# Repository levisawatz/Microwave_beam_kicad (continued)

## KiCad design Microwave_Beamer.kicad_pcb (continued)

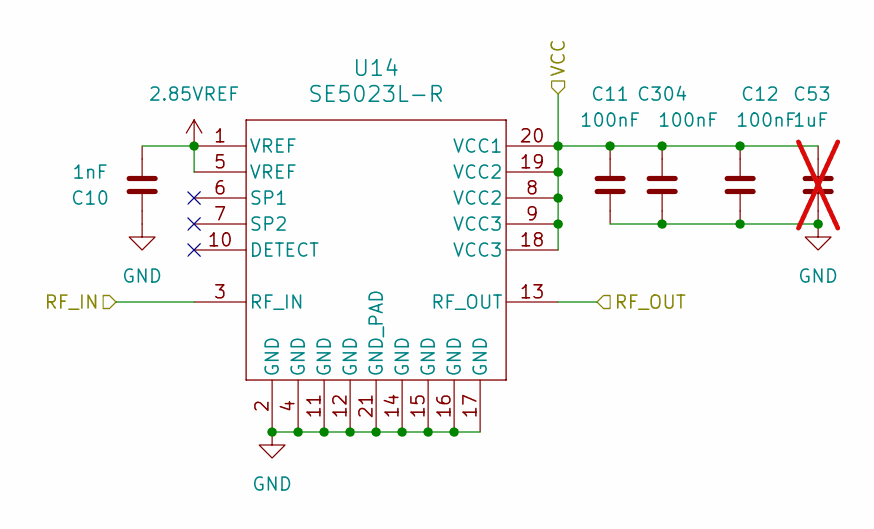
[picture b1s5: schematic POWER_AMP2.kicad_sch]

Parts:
C10: 1nF; C_0402_1005Metric; MPN GCM1555C1H102GA16J
C11, C12, C304: 100nF; C_0402_1005Metric; MPN GCM155R71H104KE02J
C53: 1uF; C_0603_1608Metric; MPN GRT188R61H105KE13D; not fitted
U14: SE5023L-R; QFN20_4X4_STM; MPN SE5023L-R

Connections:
2.85VREF: C10.1, U14.1 (VREF), U14.5 (VREF); also elsewhere on the board
+5V: C11.1, C12.1, C53.1, C304.1, U14.8 (VCC2), U14.9 (VCC3), U14.18 (VCC3), U14.19 (VCC2), U14.20 (VCC1); also elsewhere on the board
/STEM/FAN_A/Antenna_2: U14.13 (RF_OUT)
/STEM/FAN_A/FANFAN A/OUT2: U14.3 (RF_IN); also elsewhere on the board
GND: C10.2, C11.2, C12.2, C53.2, C304.2, U14.2 (GND), U14.4 (GND), U14.11 (GND), U14.12 (GND), U14.14 (GND), U14.15 (GND), U14.16 (GND), U14.17 (GND), U14.21 (GND_PAD); also elsewhere on the board

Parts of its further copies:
C13, C14, C15, C16, C18, C19, C20, C21, C22, C23, C32, C33, C34, C35, C36, C37, C70, C71, C81, C82, C84, C85, C95, C96, C98, C99, C106, C107, C110, C111, C113, C114, C118, C119, C305, C306, C307, C308, C309, C310, C311, C312, C313, C314, C315, C316, C317, C318, C319, C320, C321: 100nF; C_0402_1005Metric; MPN GCM155R71H104KE02J
C17, C31, C52, C66, C80, C94, C108, C122, C136, C150, C164, C178, C192, C206, C220, C234, C248: 1nF; C_0402_1005Metric; MPN GCM1555C1H102GA16J
C54, C55, C56, C57, C58, C67, C68, C69, C72, C83, C86, C97, C100, C109, C112, C116, C120: 1uF; C_0603_1608Metric; MPN GRT188R61H105KE13D; not fitted
U15, U17, U20, U22, U24, U26, U28, U30, U32, U34, U36, U38, U40, U42, U44, U46, U48: SE5023L-R; QFN20_4X4_STM; MPN SE5023L-R

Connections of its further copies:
2.85VREF: C17.1, C31.1, C52.1, C66.1, C80.1, C94.1, C108.1, C122.1, C136.1, C150.1, C164.1, C178.1, C192.1, C206.1, C220.1, C234.1, C248.1, U15.1 (VREF), U15.5 (VREF), U17.1 (VREF), U17.5 (VREF), U20.1 (VREF), U20.5 (VREF), U22.1 (VREF), U22.5 (VREF), U24.1 (VREF), U24.5 (VREF), U26.1 (VREF), U26.5 (VREF), U28.1 (VREF), U28.5 (VREF), U30.1 (VREF), U30.5 (VREF), U32.1 (VREF), U32.5 (VREF), U34.1 (VREF), U34.5 (VREF), U36.1 (VREF), U36.5 (VREF), U38.1 (VREF), U38.5 (VREF), U40.1 (VREF), U40.5 (VREF), U42.1 (VREF), U42.5 (VREF), U44.1 (VREF), U44.5 (VREF), U46.1 (VREF), U46.5 (VREF), U48.1 (VREF), U48.5 (VREF); also elsewhere on the board
+5V: C13.1, C14.1, C15.1, C16.1, C18.1, C19.1, C20.1, C21.1, C22.1, C23.1, C32.1, C33.1, C34.1, C35.1, C36.1, C37.1, C54.1, C55.1, C56.1, C57.1, C58.1, C67.1, C68.1, C69.1, C70.1, C71.1, C72.1, C81.1, C82.1, C83.1, C84.1, C85.1, C86.1, C95.1, C96.1, C97.1, C98.1, C99.1, C100.1, C106.1, C107.1, C109.1, C110.1, C111.1, C112.1, C113.1, C114.1, C116.1, C118.1, C119.1, C120.1, C305.1, C306.1, C307.1, C308.1, C309.1, C310.1, C311.1, C312.1, C313.1, C314.1, C315.1, C316.1, C317.1, C318.1, C319.1, C320.1, C321.1, U15.8 (VCC2), U15.9 (VCC3), U15.18 (VCC3), U15.19 (VCC2), U15.20 (VCC1), U17.8 (VCC2), U17.9 (VCC3), U17.18 (VCC3), U17.19 (VCC2), U17.20 (VCC1), U20.8 (VCC2), U20.9 (VCC3), U20.18 (VCC3), U20.19 (VCC2), U20.20 (VCC1), U22.8 (VCC2), U22.9 (VCC3), U22.18 (VCC3), U22.19 (VCC2), U22.20 (VCC1), U24.8 (VCC2), U24.9 (VCC3), U24.18 (VCC3), U24.19 (VCC2), U24.20 (VCC1), U26.8 (VCC2), U26.9 (VCC3), U26.18 (VCC3), U26.19 (VCC2), U26.20 (VCC1), U28.8 (VCC2), U28.9 (VCC3), U28.18 (VCC3), U28.19 (VCC2), U28.20 (VCC1), U30.8 (VCC2), U30.9 (VCC3), U30.18 (VCC3), U30.19 (VCC2), U30.20 (VCC1), U32.8 (VCC2), U32.9 (VCC3), U32.18 (VCC3), U32.19 (VCC2), U32.20 (VCC1), U34.8 (VCC2), U34.9 (VCC3), U34.18 (VCC3), U34.19 (VCC2), U34.20 (VCC1), U36.8 (VCC2), U36.9 (VCC3), U36.18 (VCC3), U36.19 (VCC2), U36.20 (VCC1), U38.8 (VCC2), U38.9 (VCC3), U38.18 (VCC3), U38.19 (VCC2), U38.20 (VCC1), U40.8 (VCC2), U40.9 (VCC3), U40.18 (VCC3), U40.19 (VCC2), U40.20 (VCC1), U42.8 (VCC2), U42.9 (VCC3), U42.18 (VCC3), U42.19 (VCC2), U42.20 (VCC1), U44.8 (VCC2), U44.9 (VCC3), U44.18 (VCC3), U44.19 (VCC2), U44.20 (VCC1), U46.8 (VCC2), U46.9 (VCC3), U46.18 (VCC3), U46.19 (VCC2), U46.20 (VCC1), U48.8 (VCC2), U48.9 (VCC3), U48.18 (VCC3), U48.19 (VCC2), U48.20 (VCC1); also elsewhere on the board
/STEM/FAN_A/Antenna_4: U15.13 (RF_OUT)
/STEM/FAN_A/Antenna_6: U17.13 (RF_OUT)
/STEM/FAN_A/FANFAN A/OUT4: U15.3 (RF_IN); also elsewhere on the board
/STEM/FAN_A/FANFAN A/OUT6: U17.3 (RF_IN); also elsewhere on the board
/STEM/FAN_B/Antenna_2: U20.13 (RF_OUT)
/STEM/FAN_B/Antenna_4: U24.13 (RF_OUT)
/STEM/FAN_B/Antenna_6: U22.13 (RF_OUT)
/STEM/FAN_B/FANFAN A/OUT2: U20.3 (RF_IN); also elsewhere on the board
/STEM/FAN_B/FANFAN A/OUT4: U24.3 (RF_IN); also elsewhere on the board
/STEM/FAN_B/FANFAN A/OUT6: U22.3 (RF_IN); also elsewhere on the board
/STEM/FAN_C/Antenna_2: U26.13 (RF_OUT)
/STEM/FAN_C/Antenna_4: U30.13 (RF_OUT)
/STEM/FAN_C/Antenna_6: U28.13 (RF_OUT)
/STEM/FAN_C/FANFAN A/OUT2: U26.3 (RF_IN); also elsewhere on the board
/STEM/FAN_C/FANFAN A/OUT4: U30.3 (RF_IN); also elsewhere on the board
/STEM/FAN_C/FANFAN A/OUT6: U28.3 (RF_IN); also elsewhere on the board
/STEM/FAN_D/Antenna_2: U32.13 (RF_OUT)
/STEM/FAN_D/Antenna_4: U36.13 (RF_OUT)
/STEM/FAN_D/Antenna_6: U34.13 (RF_OUT)
/STEM/FAN_D/FANFAN A/OUT2: U32.3 (RF_IN); also elsewhere on the board
/STEM/FAN_D/FANFAN A/OUT4: U36.3 (RF_IN); also elsewhere on the board
/STEM/FAN_D/FANFAN A/OUT6: U34.3 (RF_IN); also elsewhere on the board
/STEM/FAN_E/Antenna_2: U38.13 (RF_OUT)
/STEM/FAN_E/Antenna_4: U42.13 (RF_OUT)
/STEM/FAN_E/Antenna_6: U40.13 (RF_OUT)
/STEM/FAN_E/FANFAN A/OUT2: U38.3 (RF_IN); also elsewhere on the board
/STEM/FAN_E/FANFAN A/OUT4: U42.3 (RF_IN); also elsewhere on the board
/STEM/FAN_E/FANFAN A/OUT6: U40.3 (RF_IN); also elsewhere on the board
/STEM/FAN_F/Antenna_2: U44.13 (RF_OUT)
/STEM/FAN_F/Antenna_4: U48.13 (RF_OUT)
/STEM/FAN_F/Antenna_6: U46.13 (RF_OUT)
/STEM/FAN_F/FANFAN A/OUT2: U44.3 (RF_IN); also elsewhere on the board
/STEM/FAN_F/FANFAN A/OUT4: U48.3 (RF_IN); also elsewhere on the board
/STEM/FAN_F/FANFAN A/OUT6: U46.3 (RF_IN); also elsewhere on the board
GND: C13.2, C14.2, C15.2, C16.2, C17.2, C18.2, C19.2, C20.2, C21.2, C22.2, C23.2, C31.2, C32.2, C33.2, C34.2, C35.2, C36.2, C37.2, C52.2, C54.2, C55.2, C56.2, C57.2, C58.2, C66.2, C67.2, C68.2, C69.2, C70.2, C71.2, C72.2, C80.2, C81.2, C82.2, C83.2, C84.2, C85.2, C86.2, C94.2, C95.2, C96.2, C97.2, C98.2, C99.2, C100.2, C106.2, C107.2, C108.2, C109.2, C110.2, C111.2, C112.2, C113.2, C114.2, C116.2, C118.2, C119.2, C120.2, C122.2, C136.2, C150.2, C164.2, C178.2, C192.2, C206.2, C220.2, C234.2, C248.2, C305.2, C306.2, C307.2, C308.2, C309.2, C310.2, C311.2, C312.2, C313.2, C314.2, C315.2, C316.2, C317.2, C318.2, C319.2, C320.2, C321.2, U15.2 (GND), U15.4 (GND), U15.11 (GND), U15.12 (GND), U15.14 (GND), U15.15 (GND), U15.16 (GND), U15.17 (GND), U15.21 (GND_PAD), U17.2 (GND), U17.4 (GND), U17.11 (GND), U17.12 (GND), U17.14 (GND), U17.15 (GND), U17.16 (GND), U17.17 (GND), U17.21 (GND_PAD), U20.2 (GND), U20.4 (GND), U20.11 (GND), U20.12 (GND), U20.14 (GND), U20.15 (GND), U20.16 (GND), U20.17 (GND), U20.21 (GND_PAD), U22.2 (GND), U22.4 (GND), U22.11 (GND), U22.12 (GND), U22.14 (GND), U22.15 (GND), U22.16 (GND), U22.17 (GND), U22.21 (GND_PAD), U24.2 (GND), U24.4 (GND), U24.11 (GND), U24.12 (GND), U24.14 (GND), U24.15 (GND), U24.16 (GND), U24.17 (GND), U24.21 (GND_PAD), U26.2 (GND), U26.4 (GND), U26.11 (GND), U26.12 (GND), U26.14 (GND), U26.15 (GND), U26.16 (GND), U26.17 (GND), U26.21 (GND_PAD), U28.2 (GND), U28.4 (GND), U28.11 (GND), U28.12 (GND), U28.14 (GND), U28.15 (GND), U28.16 (GND), U28.17 (GND), U28.21 (GND_PAD), U30.2 (GND), U30.4 (GND), U30.11 (GND), U30.12 (GND), U30.14 (GND), U30.15 (GND), U30.16 (GND), U30.17 (GND), U30.21 (GND_PAD), U32.2 (GND), U32.4 (GND), U32.11 (GND), U32.12 (GND), U32.14 (GND), U32.15 (GND), U32.16 (GND), U32.17 (GND), U32.21 (GND_PAD), U34.2 (GND), U34.4 (GND), U34.11 (GND), U34.12 (GND), U34.14 (GND), U34.15 (GND), U34.16 (GND), U34.17 (GND), U34.21 (GND_PAD), U36.2 (GND), U36.4 (GND), U36.11 (GND), U36.12 (GND), U36.14 (GND), U36.15 (GND), U36.16 (GND), U36.17 (GND), U36.21 (GND_PAD), U38.2 (GND), U38.4 (GND), U38.11 (GND), U38.12 (GND), U38.14 (GND), U38.15 (GND), U38.16 (GND), U38.17 (GND), U38.21 (GND_PAD), U40.2 (GND), U40.4 (GND), U40.11 (GND), U40.12 (GND), U40.14 (GND), U40.15 (GND), U40.16 (GND), U40.17 (GND), U40.21 (GND_PAD), U42.2 (GND), U42.4 (GND), U42.11 (GND), U42.12 (GND), U42.14 (GND), U42.15 (GND), U42.16 (GND), U42.17 (GND), U42.21 (GND_PAD), U44.2 (GND), U44.4 (GND), U44.11 (GND), U44.12 (GND), U44.14 (GND), U44.15 (GND), U44.16 (GND), U44.17 (GND), U44.21 (GND_PAD), U46.2 (GND), U46.4 (GND), U46.11 (GND), U46.12 (GND), U46.14 (GND), U46.15 (GND), U46.16 (GND), U46.17 (GND), U46.21 (GND_PAD), U48.2 (GND), U48.4 (GND), U48.11 (GND), U48.12 (GND), U48.14 (GND), U48.15 (GND), U48.16 (GND), U48.17 (GND), U48.21 (GND_PAD); also elsewhere on the board

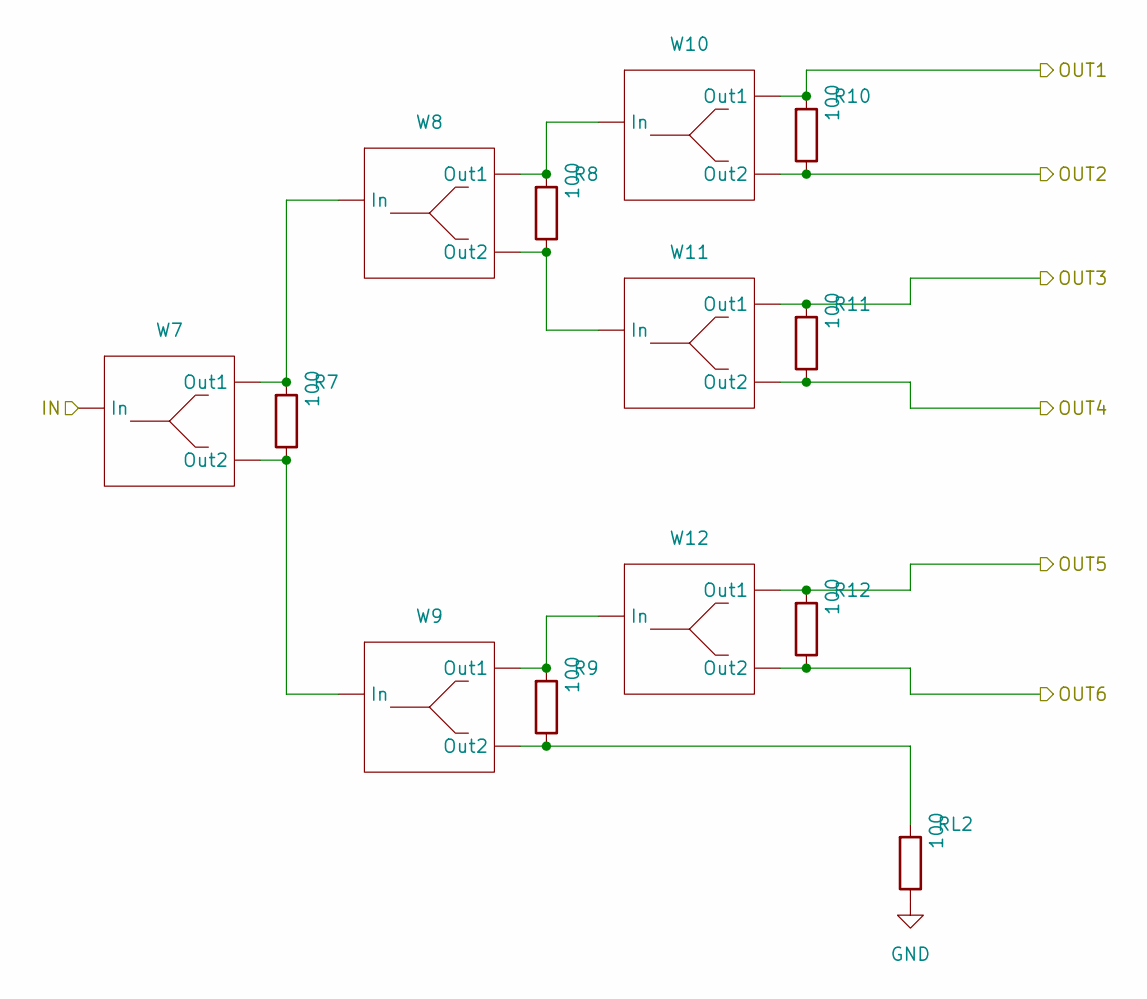
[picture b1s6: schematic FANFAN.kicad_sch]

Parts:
R7, R8, R9, R10, R11, R12: 100; R_0402_1005Metric; MPN ERA-2AED101X
RL2: 100; R_0402_1005Metric; MPN ERA-2AED101X
W7, W8, W9, W10, W11, W12: 50-70.7 Y

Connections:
/STEM/FAN_A/FANFAN A/OUT1: R10.1, W10.2 (Out1); also elsewhere on the board
/STEM/FAN_A/FANFAN A/OUT2: R10.2, W10.3 (Out2); also elsewhere on the board
/STEM/FAN_A/FANFAN A/OUT3: R11.1, W11.2 (Out1); also elsewhere on the board
/STEM/FAN_A/FANFAN A/OUT4: R11.2, W11.3 (Out2); also elsewhere on the board
/STEM/FAN_A/FANFAN A/OUT5: R12.1, W12.2 (Out1); also elsewhere on the board
/STEM/FAN_A/FANFAN A/OUT6: R12.2, W12.3 (Out2); also elsewhere on the board
/STEM/FAN_A/IN: W7.1 (In); also elsewhere on the board
GND: RL2.2; also elsewhere on the board
unnamed: R7.1, W7.2 (Out1), W8.1 (In)
unnamed: R7.2, W7.3 (Out2), W9.1 (In)
unnamed: R9.2, RL2.1, W9.3 (Out2)
unnamed: R8.1, W8.2 (Out1), W10.1 (In)
unnamed: R8.2, W8.3 (Out2), W11.1 (In)
unnamed: R9.1, W9.2 (Out1), W12.1 (In)

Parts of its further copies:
R13, R14, R15, R16, R17, R18, R19, R20, R21, R22, R23, R24, R25, R26, R27, R28, R29, R30, R31, R32, R33, R34, R35, R36, R37, R38, R39, R40, R41, R42: 100; R_0402_1005Metric; MPN ERA-2AED101X

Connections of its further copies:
/STEM/FAN_B/FANFAN A/OUT1: R16.1; also elsewhere on the board
/STEM/FAN_B/FANFAN A/OUT2: R16.2; also elsewhere on the board
/STEM/FAN_B/FANFAN A/OUT3: R17.1; also elsewhere on the board
/STEM/FAN_B/FANFAN A/OUT4: R17.2; also elsewhere on the board
/STEM/FAN_B/FANFAN A/OUT5: R18.1; also elsewhere on the board
/STEM/FAN_B/FANFAN A/OUT6: R18.2; also elsewhere on the board
/STEM/FAN_C/FANFAN A/OUT1: R22.1; also elsewhere on the board
/STEM/FAN_C/FANFAN A/OUT2: R22.2; also elsewhere on the board
/STEM/FAN_C/FANFAN A/OUT3: R23.1; also elsewhere on the board
/STEM/FAN_C/FANFAN A/OUT4: R23.2; also elsewhere on the board
/STEM/FAN_C/FANFAN A/OUT5: R24.1; also elsewhere on the board
/STEM/FAN_C/FANFAN A/OUT6: R24.2; also elsewhere on the board
/STEM/FAN_D/FANFAN A/OUT1: R28.1; also elsewhere on the board
/STEM/FAN_D/FANFAN A/OUT2: R28.2; also elsewhere on the board
/STEM/FAN_D/FANFAN A/OUT3: R29.1; also elsewhere on the board
/STEM/FAN_D/FANFAN A/OUT4: R29.2; also elsewhere on the board
/STEM/FAN_D/FANFAN A/OUT5: R30.1; also elsewhere on the board
/STEM/FAN_D/FANFAN A/OUT6: R30.2; also elsewhere on the board
/STEM/FAN_E/FANFAN A/OUT1: R34.1; also elsewhere on the board
/STEM/FAN_E/FANFAN A/OUT2: R34.2; also elsewhere on the board
/STEM/FAN_E/FANFAN A/OUT3: R35.1; also elsewhere on the board
/STEM/FAN_E/FANFAN A/OUT4: R35.2; also elsewhere on the board
/STEM/FAN_E/FANFAN A/OUT5: R36.1; also elsewhere on the board
/STEM/FAN_E/FANFAN A/OUT6: R36.2; also elsewhere on the board
/STEM/FAN_F/FANFAN A/OUT1: R40.1; also elsewhere on the board
/STEM/FAN_F/FANFAN A/OUT2: R40.2; also elsewhere on the board
/STEM/FAN_F/FANFAN A/OUT3: R41.1; also elsewhere on the board
/STEM/FAN_F/FANFAN A/OUT4: R41.2; also elsewhere on the board
/STEM/FAN_F/FANFAN A/OUT5: R42.1; also elsewhere on the board
/STEM/FAN_F/FANFAN A/OUT6: R42.2; also elsewhere on the board
unnamed 213: R13.1; also elsewhere on the board
unnamed 214: R13.2; also elsewhere on the board
unnamed 215: R14.1; also elsewhere on the board
unnamed 216: R14.2; also elsewhere on the board
unnamed 217: R15.1; also elsewhere on the board
unnamed 218: R15.2; also elsewhere on the board
unnamed 219: R19.1; also elsewhere on the board
unnamed 220: R19.2; also elsewhere on the board
unnamed 221: R20.1; also elsewhere on the board
unnamed 222: R20.2; also elsewhere on the board
unnamed 223: R21.1; also elsewhere on the board
unnamed 224: R21.2; also elsewhere on the board
unnamed 225: R25.1; also elsewhere on the board
unnamed 226: R25.2; also elsewhere on the board
unnamed 227: R26.1; also elsewhere on the board
unnamed 228: R26.2; also elsewhere on the board
unnamed 229: R27.1; also elsewhere on the board
unnamed 230: R27.2; also elsewhere on the board
unnamed 231: R31.1; also elsewhere on the board
unnamed 232: R31.2; also elsewhere on the board
unnamed 233: R32.1; also elsewhere on the board
unnamed 234: R32.2; also elsewhere on the board
unnamed 235: R33.1; also elsewhere on the board
unnamed 236: R33.2; also elsewhere on the board
unnamed 237: R37.1; also elsewhere on the board
unnamed 238: R37.2; also elsewhere on the board
unnamed 239: R38.1; also elsewhere on the board
unnamed 240: R38.2; also elsewhere on the board
unnamed 241: R39.1; also elsewhere on the board
unnamed 242: R39.2; also elsewhere on the board

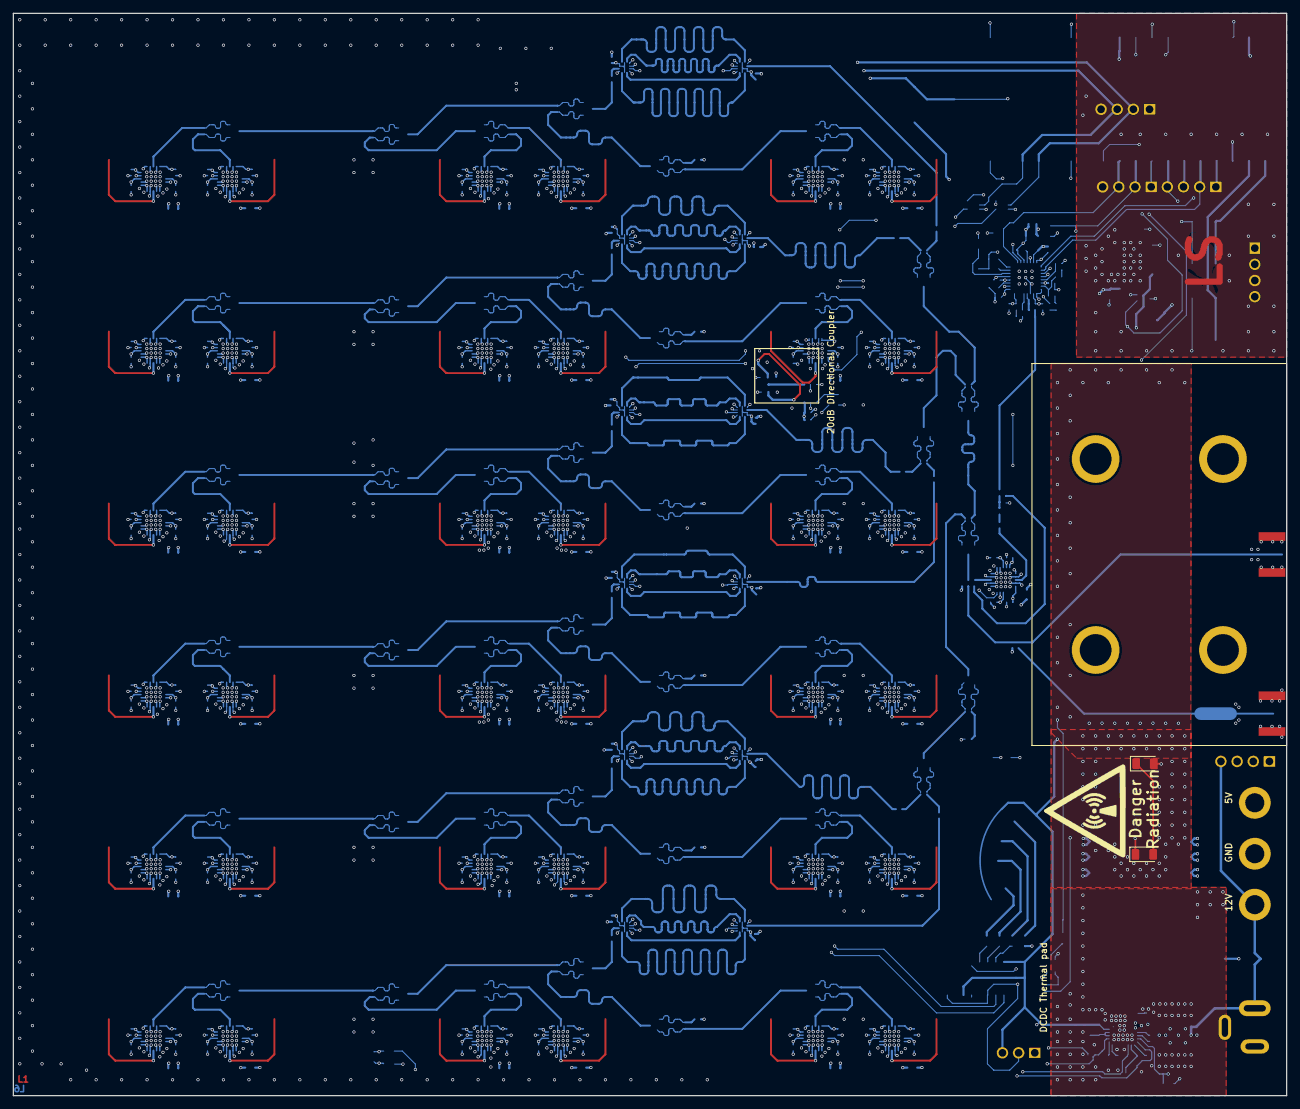
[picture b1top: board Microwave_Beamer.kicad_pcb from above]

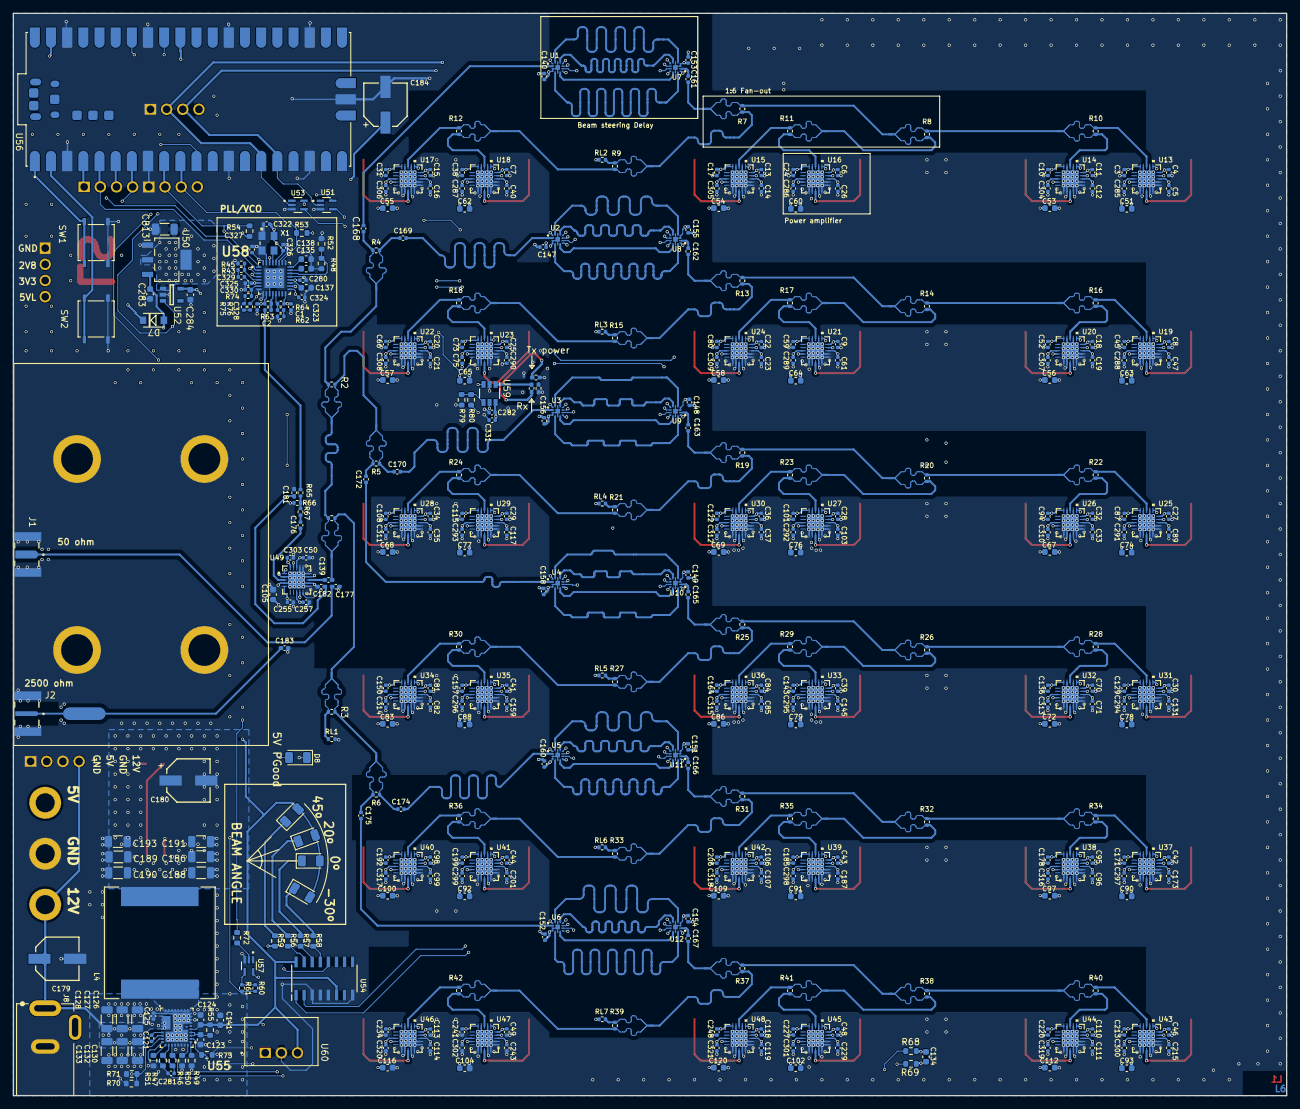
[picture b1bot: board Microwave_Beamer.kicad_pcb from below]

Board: 6 copper layers, 200.0 x 170.0 mm, 473 parts (464 on the bottom side), 198 nets.

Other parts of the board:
RL3, RL4, RL5, RL6, RL7: 50; R_0402_1005Metric
W13, W14, W15, W16, W17, W18, W19, W20, W21, W22, W23, W24, W25, W26, W27, W28, W29, W30, W31, W32, W33, W34, W35, W36, W37, W38, W39, W40, W41, W42: splitter; 50-70.7 Y

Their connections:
/STEM/FAN_B/FANFAN A/OUT1: W16.2 (Out1); also elsewhere on the board
/STEM/FAN_B/FANFAN A/OUT2: W16.3 (Out2); also elsewhere on the board
/STEM/FAN_B/FANFAN A/OUT3: W17.2 (Out1); also elsewhere on the board
/STEM/FAN_B/FANFAN A/OUT4: W17.3 (Out2); also elsewhere on the board
/STEM/FAN_B/FANFAN A/OUT5: W18.2 (Out1); also elsewhere on the board
/STEM/FAN_B/FANFAN A/OUT6: W18.3 (Out2); also elsewhere on the board
/STEM/FAN_B/IN: W13.1 (In); also elsewhere on the board
/STEM/FAN_C/FANFAN A/OUT1: W22.2 (Out1); also elsewhere on the board
/STEM/FAN_C/FANFAN A/OUT2: W22.3 (Out2); also elsewhere on the board
/STEM/FAN_C/FANFAN A/OUT3: W23.2 (Out1); also elsewhere on the board
/STEM/FAN_C/FANFAN A/OUT4: W23.3 (Out2); also elsewhere on the board
/STEM/FAN_C/FANFAN A/OUT5: W24.2 (Out1); also elsewhere on the board
/STEM/FAN_C/FANFAN A/OUT6: W24.3 (Out2); also elsewhere on the board
/STEM/FAN_C/IN: W19.1 (In); also elsewhere on the board
/STEM/FAN_D/FANFAN A/OUT1: W28.2 (Out1); also elsewhere on the board
/STEM/FAN_D/FANFAN A/OUT2: W28.3 (Out2); also elsewhere on the board
/STEM/FAN_D/FANFAN A/OUT3: W29.2 (Out1); also elsewhere on the board
/STEM/FAN_D/FANFAN A/OUT4: W29.3 (Out2); also elsewhere on the board
/STEM/FAN_D/FANFAN A/OUT5: W30.2 (Out1); also elsewhere on the board
/STEM/FAN_D/FANFAN A/OUT6: W30.3 (Out2); also elsewhere on the board
/STEM/FAN_D/IN: W25.1 (In); also elsewhere on the board
/STEM/FAN_E/FANFAN A/OUT1: W34.2 (Out1); also elsewhere on the board
/STEM/FAN_E/FANFAN A/OUT2: W34.3 (Out2); also elsewhere on the board
/STEM/FAN_E/FANFAN A/OUT3: W35.2 (Out1); also elsewhere on the board
/STEM/FAN_E/FANFAN A/OUT4: W35.3 (Out2); also elsewhere on the board
/STEM/FAN_E/FANFAN A/OUT5: W36.2 (Out1); also elsewhere on the board
/STEM/FAN_E/FANFAN A/OUT6: W36.3 (Out2); also elsewhere on the board
/STEM/FAN_E/IN: W31.1 (In); also elsewhere on the board
/STEM/FAN_F/FANFAN A/OUT1: W40.2 (Out1); also elsewhere on the board
/STEM/FAN_F/FANFAN A/OUT2: W40.3 (Out2); also elsewhere on the board
/STEM/FAN_F/FANFAN A/OUT3: W41.2 (Out1); also elsewhere on the board
/STEM/FAN_F/FANFAN A/OUT4: W41.3 (Out2); also elsewhere on the board
/STEM/FAN_F/FANFAN A/OUT5: W42.2 (Out1); also elsewhere on the board
/STEM/FAN_F/FANFAN A/OUT6: W42.3 (Out2); also elsewhere on the board
/STEM/FAN_F/IN: W37.1 (In); also elsewhere on the board
GND: RL3.2, RL4.2, RL5.2, RL6.2, RL7.2; also elsewhere on the board
unnamed 213: W13.2 (Out1), W14.1 (In); also elsewhere on the board
unnamed 214: W13.3 (Out2), W15.1 (In); also elsewhere on the board
unnamed 215: W14.2 (Out1), W16.1 (In); also elsewhere on the board
unnamed 216: W14.3 (Out2), W17.1 (In); also elsewhere on the board
unnamed 217: W15.2 (Out1), W18.1 (In); also elsewhere on the board
unnamed 218: RL3.1, W15.3 (Out2); also elsewhere on the board
unnamed 219: W19.2 (Out1), W20.1 (In); also elsewhere on the board
unnamed 220: W19.3 (Out2), W21.1 (In); also elsewhere on the board
unnamed 221: W20.2 (Out1), W22.1 (In); also elsewhere on the board
unnamed 222: W20.3 (Out2), W23.1 (In); also elsewhere on the board
unnamed 223: W21.2 (Out1), W24.1 (In); also elsewhere on the board
unnamed 224: RL4.1, W21.3 (Out2); also elsewhere on the board
unnamed 225: W25.2 (Out1), W26.1 (In); also elsewhere on the board
unnamed 226: W25.3 (Out2), W27.1 (In); also elsewhere on the board
unnamed 227: W26.2 (Out1), W28.1 (In); also elsewhere on the board
unnamed 228: W26.3 (Out2), W29.1 (In); also elsewhere on the board
unnamed 229: W27.2 (Out1), W30.1 (In); also elsewhere on the board
unnamed 230: RL5.1, W27.3 (Out2); also elsewhere on the board
unnamed 231: W31.2 (Out1), W32.1 (In); also elsewhere on the board
unnamed 232: W31.3 (Out2), W33.1 (In); also elsewhere on the board
unnamed 233: W32.2 (Out1), W34.1 (In); also elsewhere on the board
unnamed 234: W32.3 (Out2), W35.1 (In); also elsewhere on the board
unnamed 235: W33.2 (Out1), W36.1 (In); also elsewhere on the board
unnamed 236: RL6.1, W33.3 (Out2); also elsewhere on the board
unnamed 237: W37.2 (Out1), W38.1 (In); also elsewhere on the board
unnamed 238: W37.3 (Out2), W39.1 (In); also elsewhere on the board
unnamed 239: W38.2 (Out1), W40.1 (In); also elsewhere on the board
unnamed 240: W38.3 (Out2), W41.1 (In); also elsewhere on the board
unnamed 241: W39.2 (Out1), W42.1 (In); also elsewhere on the board
unnamed 242: RL7.1, W39.3 (Out2); also elsewhere on the board

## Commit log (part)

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2026-04-08 skdja7rkweg
2026-05-03 moving along
2026-05-04 6 layers now
2026-05-24 completed length matching
2026-06-27 june_26
